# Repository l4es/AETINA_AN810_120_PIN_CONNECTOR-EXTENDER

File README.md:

# AETINA_AN810_120_PIN_CONNECTOR-EXTENDER
Extension of 120-pin camera connector on Aetina AN810 carrier board (pinout is compatible with 120-pin camera connector on TX2/Xavier AGX Devkits)

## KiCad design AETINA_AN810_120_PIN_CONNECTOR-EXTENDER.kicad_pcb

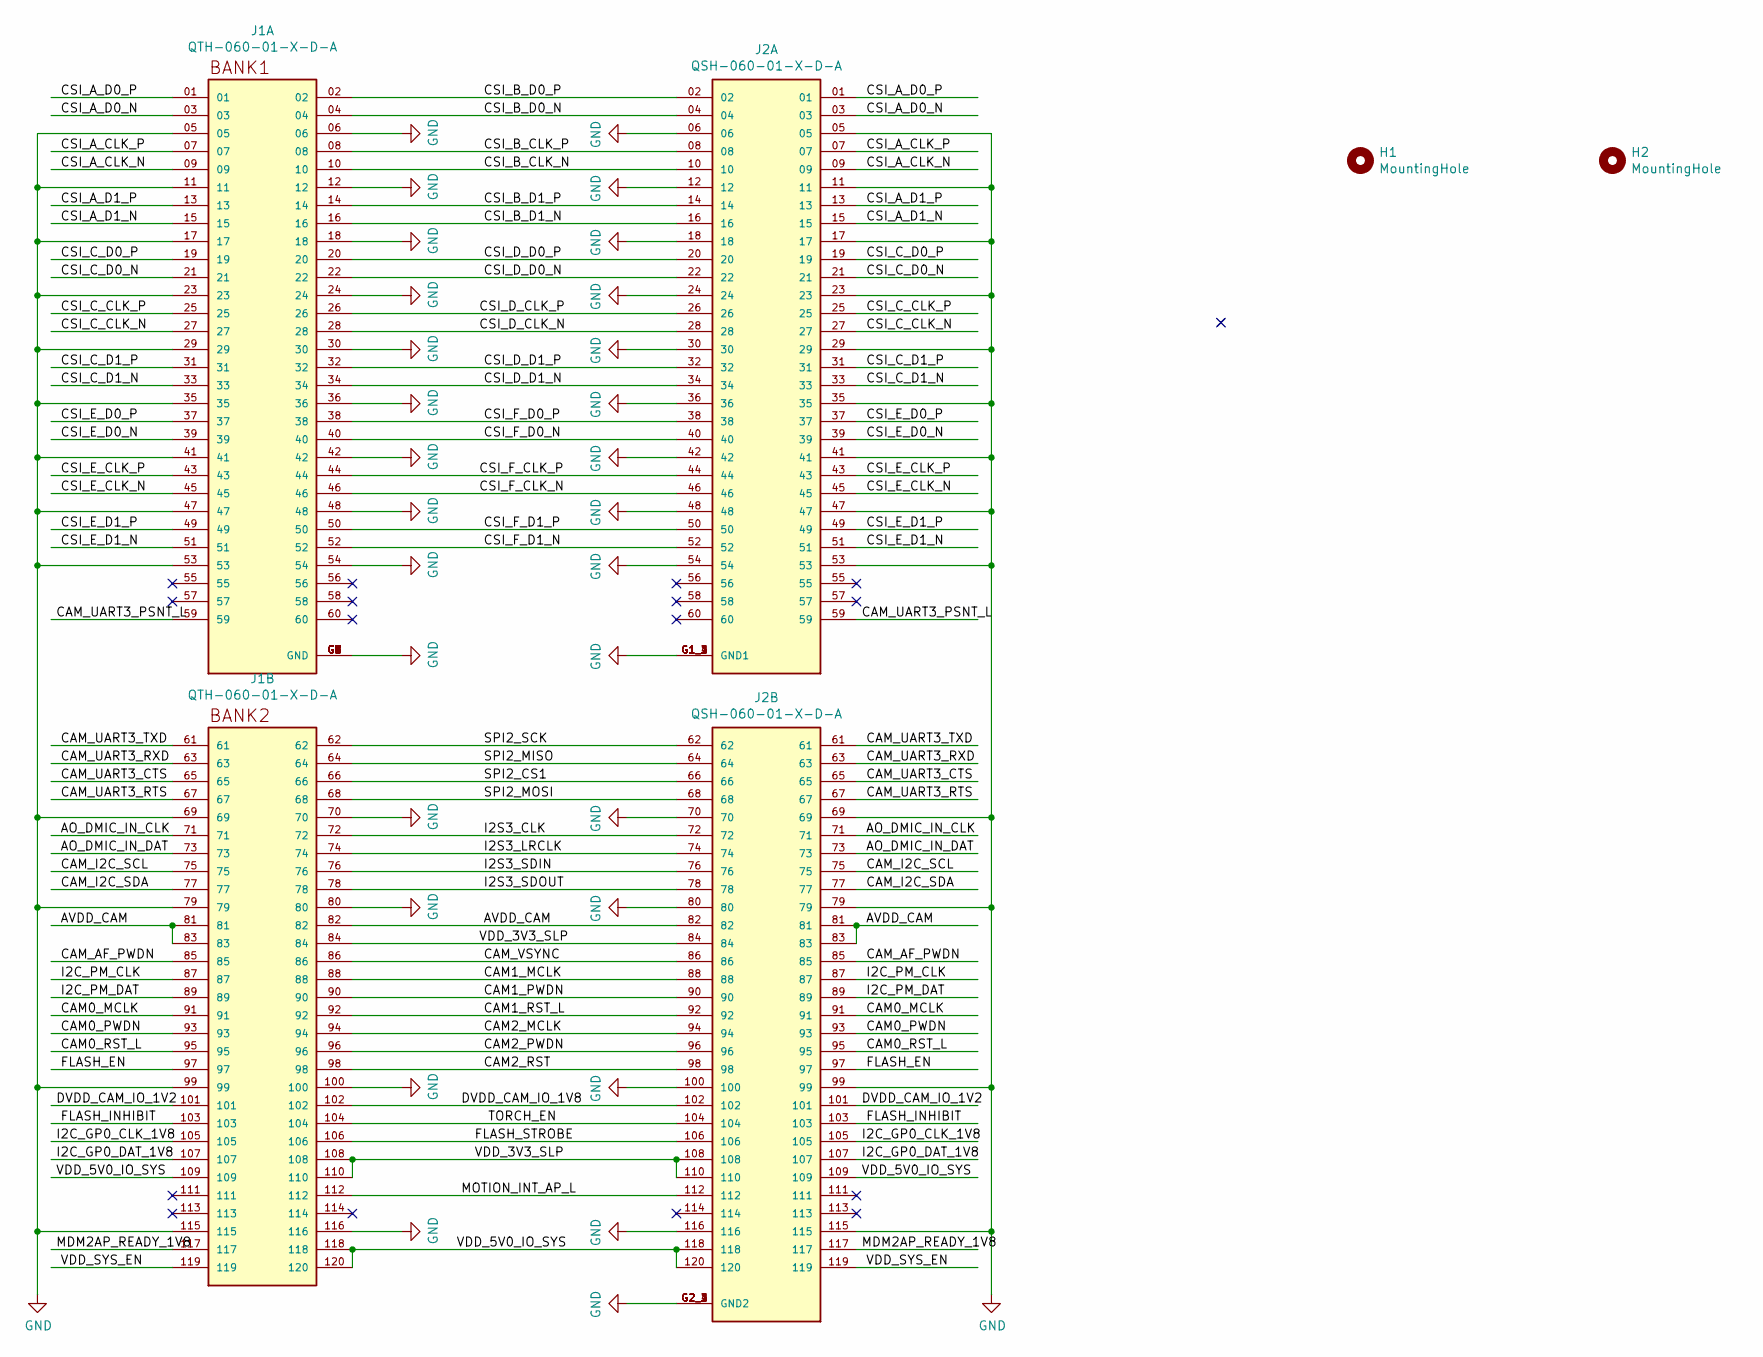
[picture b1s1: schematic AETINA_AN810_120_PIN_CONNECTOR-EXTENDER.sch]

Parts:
H1, H2: MountingHole; MountingHole_3.2mm_M3
J1: QTH-060-01-X-D-A; SAMTEC_QTH-060-01-X-D-A; PARTREV L
J2: QSH-060-01-X-D-A; SAMTEC_QSH-060-01-X-D-A; PARTREV M

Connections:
/AO_DMIC_IN_CLK: J1.71, J2.71
/AO_DMIC_IN_DAT: J1.73, J2.73
/AVDD_CAM: J1.81, J1.82, J1.83, J2.81, J2.82, J2.83
/CAM0_MCLK: J1.91, J2.91
/CAM0_PWDN: J1.93, J2.93
/CAM0_RST_L: J1.95, J2.95
/CAM1_MCLK: J1.88, J2.88
/CAM1_PWDN: J1.90, J2.90
/CAM1_RST_L: J1.92, J2.92
/CAM2_MCLK: J1.94, J2.94
/CAM2_PWDN: J1.96, J2.96
/CAM2_RST: J1.98, J2.98
/CAM_AF_PWDN: J1.85, J2.85
/CAM_I2C_SCL: J1.75, J2.75
/CAM_I2C_SDA: J1.77, J2.77
/CAM_UART3_CTS: J1.65, J2.65
/CAM_UART3_PSNT_L: J1.59, J2.59
/CAM_UART3_RTS: J1.67, J2.67
/CAM_UART3_RXD: J1.63, J2.63
/CAM_UART3_TXD: J1.61, J2.61
/CAM_VSYNC: J1.86, J2.86
/CSI_A_CLK_N: J1.09, J2.09
/CSI_A_CLK_P: J1.07, J2.07
/CSI_A_D0_N: J1.03, J2.03
/CSI_A_D0_P: J1.01, J2.01
/CSI_A_D1_N: J1.15, J2.15
/CSI_A_D1_P: J1.13, J2.13
/CSI_B_CLK_N: J1.10, J2.10
/CSI_B_CLK_P: J1.08, J2.08
/CSI_B_D0_N: J1.04, J2.04
/CSI_B_D0_P: J1.02, J2.02
/CSI_B_D1_N: J1.16, J2.16
/CSI_B_D1_P: J1.14, J2.14
/CSI_C_CLK_N: J1.27, J2.27
/CSI_C_CLK_P: J1.25, J2.25
/CSI_C_D0_N: J1.21, J2.21
/CSI_C_D0_P: J1.19, J2.19
/CSI_C_D1_N: J1.33, J2.33
/CSI_C_D1_P: J1.31, J2.31
/CSI_D_CLK_N: J1.28, J2.28
/CSI_D_CLK_P: J1.26, J2.26
/CSI_D_D0_N: J1.22, J2.22
/CSI_D_D0_P: J1.20, J2.20
/CSI_D_D1_N: J1.34, J2.34
/CSI_D_D1_P: J1.32, J2.32
/CSI_E_CLK_N: J1.45, J2.45
/CSI_E_CLK_P: J1.43, J2.43
/CSI_E_D0_N: J1.39, J2.39
/CSI_E_D0_P: J1.37, J2.37
/CSI_E_D1_N: J1.51, J2.51
/CSI_E_D1_P: J1.49, J2.49
/CSI_F_CLK_N: J1.46, J2.46
/CSI_F_CLK_P: J1.44, J2.44
/CSI_F_D0_N: J1.40, J2.40
/CSI_F_D0_P: J1.38, J2.38
/CSI_F_D1_N: J1.52, J2.52
/CSI_F_D1_P: J1.50, J2.50
/DVDD_CAM_IO_1V2: J1.101, J2.101
/DVDD_CAM_IO_1V8: J1.102, J2.102
/FLASH_EN: J1.97, J2.97
/FLASH_INHIBIT: J1.103, J2.103
/FLASH_STROBE: J1.106, J2.106
/I2C_GP0_CLK_1V8: J1.105, J2.105
/I2C_GP0_DAT_1V8: J1.107, J2.107
/I2C_PM_CLK: J1.87, J2.87
/I2C_PM_DAT: J1.89, J2.89
/I2S3_CLK: J1.72, J2.72
/I2S3_LRCLK: J1.74, J2.74
/I2S3_SDIN: J1.76, J2.76
/I2S3_SDOUT: J1.78, J2.78
/MDM2AP_READY_1V8: J1.117, J2.117
/MOTION_INT_AP_L: J1.112, J2.112
/SPI2_CS1: J1.66, J2.66
/SPI2_MISO: J1.64, J2.64
/SPI2_MOSI: J1.68, J2.68
/SPI2_SCK: J1.62, J2.62
/TORCH_EN: J1.104, J2.104
/VDD_3V3_SLP: J1.84, J1.108, J1.110, J2.84, J2.108, J2.110
/VDD_5V0_IO_SYS: J1.109, J1.118, J1.120, J2.109, J2.118, J2.120
/VDD_SYS_EN: J1.119, J2.119
GND: J1.05, J1.06, J1.11, J1.12, J1.17, J1.18, J1.23, J1.24, J1.29, J1.30, J1.35, J1.36, J1.41, J1.42, J1.47, J1.48, J1.53, J1.54, J1.69, J1.70, J1.79, J1.80, J1.99, J1.100, J1.115, J1.116, J1.G1 (GND), J1.G2 (GND), J1.G3 (GND), J1.G4 (GND), J1.G5 (GND), J1.G6 (GND), J1.G7 (GND), J1.G8 (GND), J2.05, J2.06, J2.11, J2.12, J2.17, J2.18, J2.23, J2.24, J2.29, J2.30, J2.35, J2.36, J2.41, J2.42, J2.47, J2.48, J2.53, J2.54, J2.69, J2.70, J2.79, J2.80, J2.99, J2.100, J2.115, J2.116, J2.G1_1 (GND1), J2.G1_2 (GND1), J2.G1_3 (GND1), J2.G1_4 (GND1), J2.G2_1 (GND2), J2.G2_2 (GND2), J2.G2_3 (GND2), J2.G2_4 (GND2)

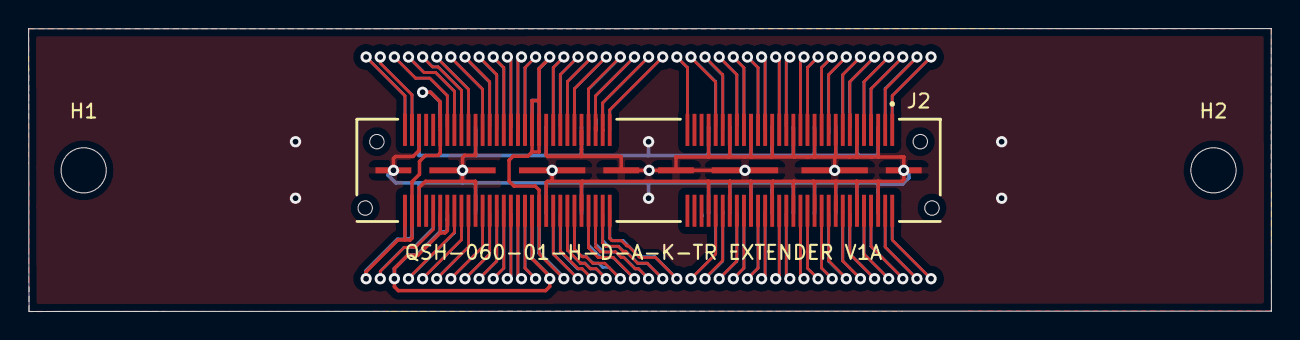
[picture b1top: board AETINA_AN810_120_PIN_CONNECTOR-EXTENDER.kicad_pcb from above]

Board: 2 copper layers, 88.0 x 20.0 mm, 4 parts (1 on the bottom side), 81 nets.

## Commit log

2021-12-09 Initial commit, placing completed
2021-12-10 Routing completed
2021-12-11 Fix wrong wiring by referring to incorrect connector
2021-12-11 Release V1A
2021-12-12 Add documentation
2021-12-12 Add README with illustration
